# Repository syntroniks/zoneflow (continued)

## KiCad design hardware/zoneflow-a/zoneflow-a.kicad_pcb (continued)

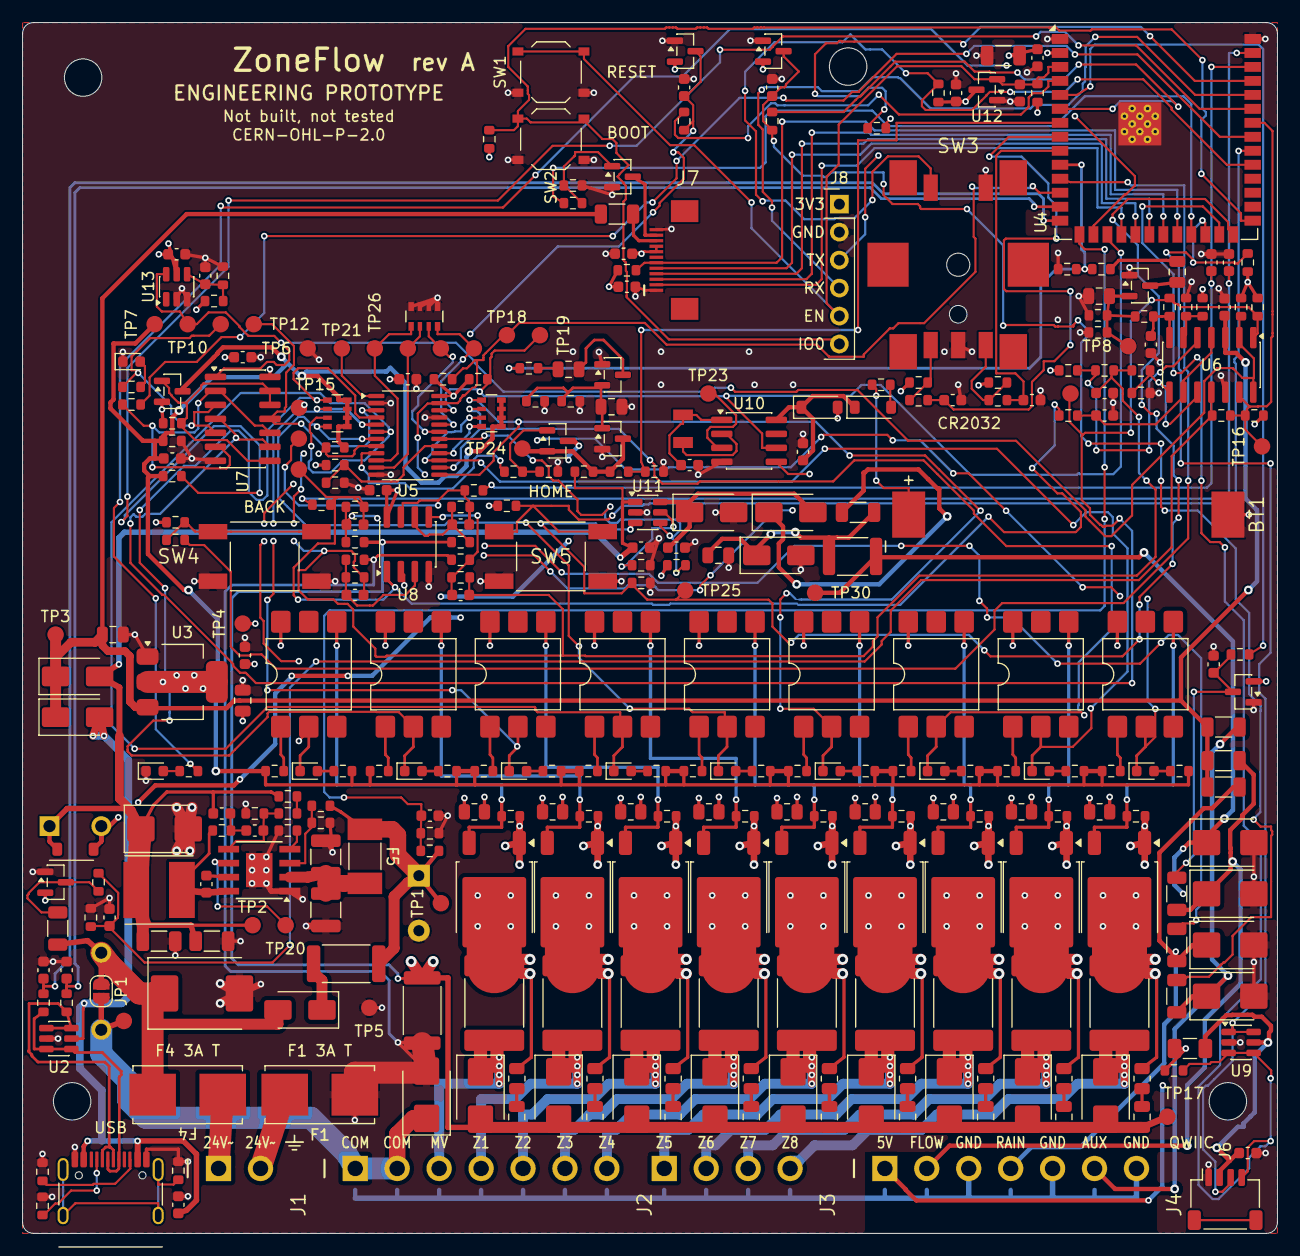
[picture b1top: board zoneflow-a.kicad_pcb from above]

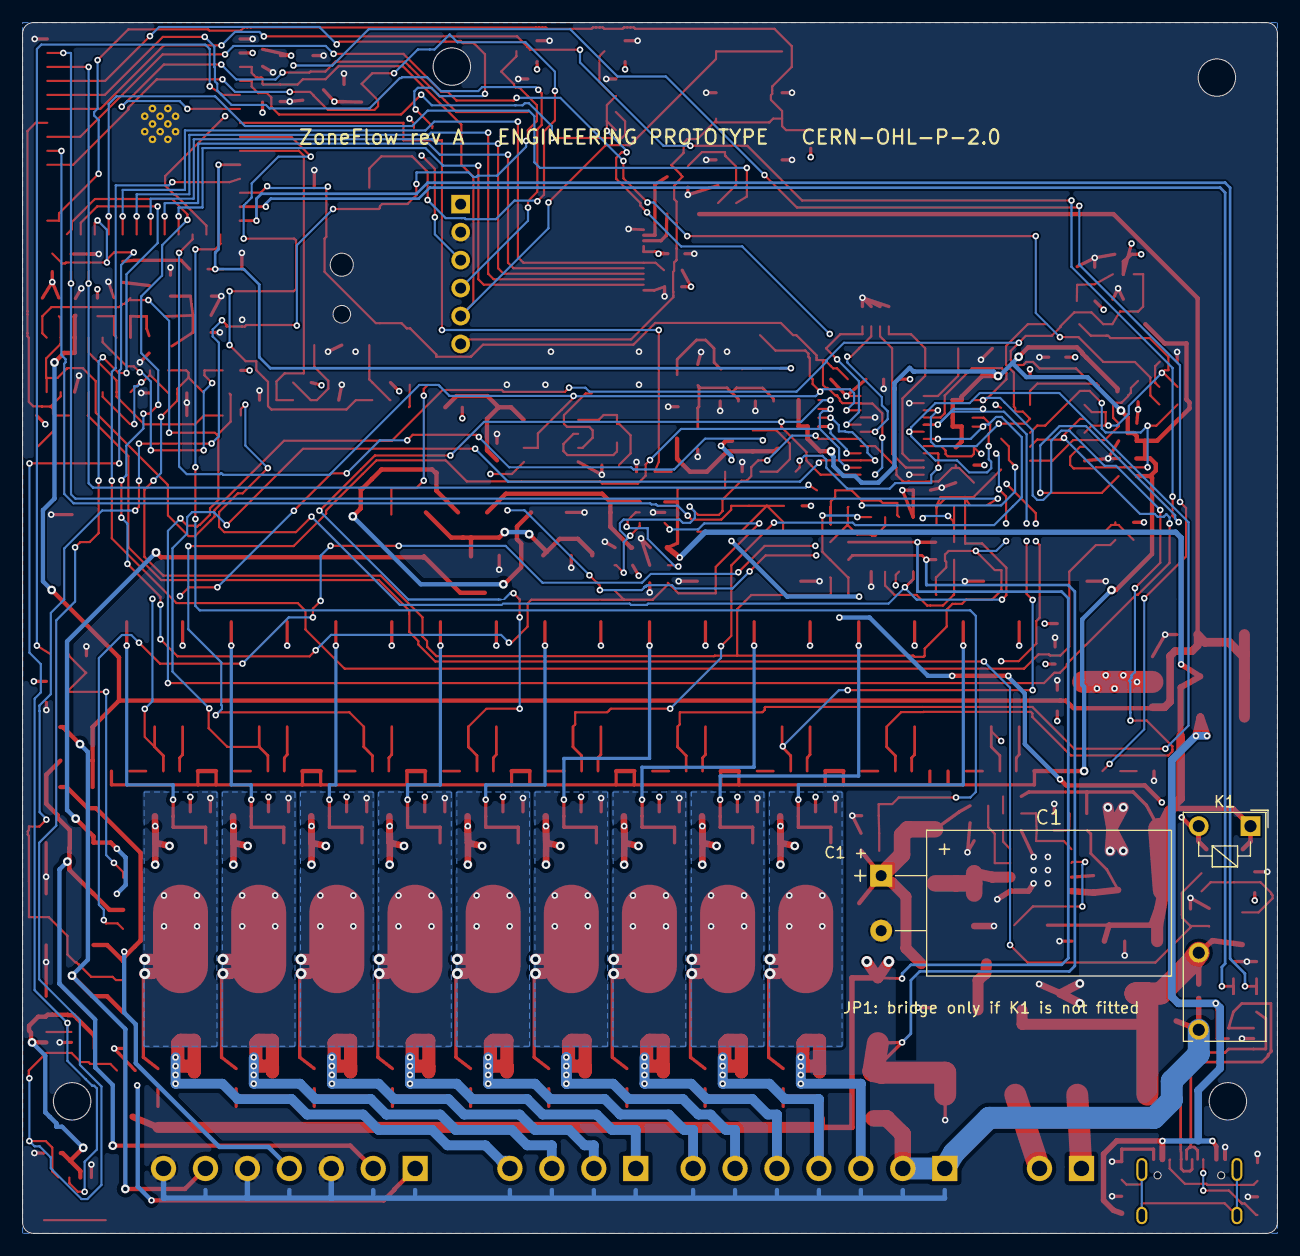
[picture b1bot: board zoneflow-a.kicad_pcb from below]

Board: 4 copper layers, 114.0 x 110.0 mm, 351 parts (2 on the bottom side), 198 nets.

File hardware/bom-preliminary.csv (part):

refs,qty_8zone,qty_4zone,value,package,manufacturer,mpn,lcsc,jlcpcb_library,jlcpcb_stock,usd_each_at_10,usd_each_at_100,usd_each_at_1000,source_url,datasheet_url,datasheet,date_checked,note
J1,1,1,"Header 2-way 3.81 mm pluggable, right angle",THT,Cixi Kefa Elec,KF2EDGR-3.81-2P,C441182,extended,45747,0.0537,0.0436,0.03,https://www.lcsc.com/product-detail/pluggable-system-termina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,https://www.lcsc.com/datasheet/lcsc_datasheet_2303311930_Cix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,listing only,2026-11-10,Mates with plug KF2EDGK-3.81-2P
F1 F4,2,2,Fuse 3 A time-lag in SMD holder,SMD 9.7x5 mm,Littelfuse,0154003.DRT,C206913,extended,2514,1.5283,1.1879,1.111,https://www.lcsc.com/product-detail/disposable-fuses_littelf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,https://www.lcsc.com/datasheet/lcsc_datasheet_2401301225_Lit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,read,2026-11-10,Replacement fuse 0452003.MRL (C99550)
D1,1,1,TVS 48 V bidirectional 1500 W,SMC,Littelfuse,SMCJ48CA,C151287,extended,4645,0.2481,0.1974,0.1485,https://www.lcsc.com/product-detail/esd-and-surge-protection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,https://www.lcsc.com/datasheet/lcsc_datasheet_2304140030_Lit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,read,2026-11-10,
D2,1,1,Rectifier 1 A 1000 V,SMA,MDD(Microdiode Semiconductor),M7,C95872,basic,5405522,0.0103,0.0103,0.0085,https://www.lcsc.com/product-detail/diodes-general-purpose_m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,https://www.lcsc.com/datasheet/lcsc_datasheet_2407101107_MDD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,read,2026-11-10,
R1,1,1,"3R 5% 1 W, surge series",2512,YAGEO,SR2512JK-073RL,C2936639,extended,3972,0.1926,0.1504,0.1097,https://www.lcsc.com/product-detail/chip-resistor-surface-mo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,https://www.lcsc.com/datasheet/C2936639.pdf,read,2026-11-10,"Yageo SR series data sheet V.14, figure 7-2: about 750 W for 1 ms and 200 W for 10 ms single pulse in 2512 at 5 % tolerance. The 1 % SR2512FK parts follow figure 7-1 and take about 200 W at 1 ms, which is not enough"
C1,1,1,470 uF 63 V aluminium electrolytic,THT 12.5x20 mm,Rubycon,63ZLJ470M12.5X20,C2940725,extended,3180,0.3453,0.2537,0.2177,https://www.lcsc.com/product-detail/aluminum-electrolytic-ca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,https://www.lcsc.com/datasheet/C2940725.pdf,read,2026-11-10,"Through-hole, soldered by hand from the bottom side, lying down; not machine-fitted. Rubycon ZLJ sheet: 10000 h at 105 C, 2400 mA at 100 kHz, 1320 mA at 120 Hz. Same holes: Rubycon 63PX470MEFC12.5X20 (C88758, 2000 h, read) and AISHI ERS1JM471K20OT (C106675, listing only)"
F5,1,1,"Fuse 0.5 A very fast-acting, 125 V",2410,Littelfuse,0451.500MRL,C142836,extended,11512,0.2339,0.1908,0.1321,https://www.lcsc.com/product-detail/disposable-fuses_littelf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,https://www.lcsc.com/datasheet/lcsc_datasheet_1810280911_Lit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,read,2026-11-10,"Littelfuse 451/453 series: 0.42 ohm cold, nominal melting I2t 0.0824 A2s, interrupting 50 A at 125 V and 300 A at 32 V DC. Soldered: it opens only when U1 has failed. Do not fit a larger rating: the 0.42 ohm also limits the fault current to the interrupting rating"
C2 C3,2,2,2.2 uF 100 V X7R,1210,Samsung Electro-Mechanics,CL32B225KCJSNNE,C55151,extended,22064,0.2062,0.1658,0.1575,https://www.lcsc.com/product-detail/multilayer-ceramic-capac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,https://www.lcsc.com/datasheet/lcsc_datasheet_2304140030_Sam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,listing only,2026-11-10,
U1,1,1,LM5164DDAR 100 V 1 A synchronous buck,SO-8 PowerPAD,Texas Instruments,LM5164DDAR,C477928,extended,1840,2.1697,1.6739,1.5119,https://www.lcsc.com/product-detail/dc-dc-converters_texas-i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,https://www.ti.com/lit/ds/symlink/lm5164.pdf,read,2026-11-10,
C4,1,1,2.2 nF 50 V X7R,0603,FH (Guangdong Fenghua Advanced Tech),0603B222K500NT,C1604,basic,543476,0.0109,0.0109,0.0086,https://www.lcsc.com/product-detail/multilayer-ceramic-capac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,https://www.lcsc.com/datasheet/lcsc_datasheet_2304140030_FH-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,read,2026-11-11,"Fenghua general MLCC specification (the LCSC sheet for this number): X7R, +/-10 % (K), 50 V, -55 to 125 C, insulation resistance 10 Gohm minimum up to 25 nF. Replaces Samsung CL10B222KB8NNNC (C16033, extended) since the BOM consolidation; same value, dielectric, tolerance, voltage and package"
L1,1,1,"47 uH, Isat 2.0 A, 0.2R",6x6x4.5 mm,BOURNS,SRN6045TA-470M,C5151734,extended,4123,0.3608,0.2859,0.2047,https://www.lcsc.com/product-detail/power-inductors_bourns-s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,https://wmsc.lcsc.com/wmsc/upload/file/pdf/v2/lcsc/220825180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,read,2026-11-10,
C5 C6 C14,3,3,22 uF 25 V X5R,1206,Samsung Electro-Mechanics,CL31A226KAHNNNE,C12891,basic,1976907,0.1028,0.1028,0.0724,https://www.lcsc.com/product-detail/multilayer-ceramic-capac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,https://www.lcsc.com/datasheet/lcsc_datasheet_2304140030_Sam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,listing only,2026-11-10,
R2,1,1,47k 1%,0603,UNI-ROYAL(Uniroyal Elec),0603WAF4702T5E,C25819,basic,3006958,0.0016,0.0016,0.0012,https://www.lcsc.com/product-detail/chip-resistor-surface-mo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,https://www.lcsc.com/datasheet/lcsc_datasheet_2206010045_UNI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,listing only,2026-11-10,
R3,1,1,330k 1%,0603,UNI-ROYAL(Uniroyal Elec),0603WAF3303T5E,C23137,basic,678476,0.0016,0.0016,0.0012,https://www.lcsc.com/product-detail/chip-resistor-surface-mo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,https://www.lcsc.com/datasheet/lcsc_datasheet_2206010116_UNI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,listing only,2026-11-10,
R4 R10 R18 R19 R26 R27 R35 R36 R39 R41 R52 R53 R56 R58 R63 R69 R70 R72 R85 R87 R88 R93,22,22,10k 1%,0603,UNI-ROYAL(Uniroyal Elec),0603WAF1002T5E,C25804,basic,45615451,0.0022,0.0022,0.0018,https://www.lcsc.com/product-detail/chip-resistor-surface-mo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,https://www.lcsc.com/datasheet/lcsc_datasheet_2206010045_UNI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,listing only,2026-11-10,
R5 R12 R14 R25 R31 R62 R86 R90 R94 R96,10,10,100k 1%,0603,UNI-ROYAL(Uniroyal Elec),0603WAF1003T5E,C25803,basic,15636901,0.0029,0.0029,0.0023,https://www.lcsc.com/product-detail/chip-resistor-surface-mo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,https://www.lcsc.com/datasheet/lcsc_datasheet_2206010045_UNI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,listing only,2026-11-10,
R30 R91 R100,3,3,110k 1%,0603,UNI-ROYAL(Uniroyal Elec),0603WAF1103T5E,C25805,extended (preferred),180061,0.0028,0.0028,0.0021,https://www.lcsc.com/product-detail/chip-resistor-surface-mo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,https://www.lcsc.com/datasheet/C25805.pdf,listing only,2026-11-10,
R95,1,1,150k 1%,0603,UNI-ROYAL(Uniroyal Elec),0603WAF1503T5E,C22807,basic,701846,0.0017,0.0017,0.0013,https://www.lcsc.com/product-detail/chip-resistor-surface-mo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,https://www.lcsc.com/datasheet/C22807.pdf,listing only,2026-11-10,
RN1 RN2 RN3,3,3,100k x4 5% resistor array,0603x4,UNI-ROYAL(Uniroyal Elec),4D03WGJ0104T5E,C1996,extended,7320,0.0103,0.0103,0.0083,https://www.lcsc.com/product-detail/resistor-networks-arrays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,https://www.lcsc.com/datasheet/C1996.pdf,read,2026-11-10,"Four isolated resistors, convex 4D03. Pin pairs 1-8, 2-7, 3-6, 4-5 assumed from the usual numbering; the data sheet shows the circuit as a picture. Confirm at capture"
R6 R8 R83,3,3,200k 1%,0603,UNI-ROYAL(Uniroyal Elec),0603WAF2003T5E,C25811,basic,1820047,0.0021,0.0021,0.0016,https://www.lcsc.com/product-detail/chip-resistor-surface-mo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,https://www.lcsc.com/datasheet/lcsc_datasheet_2206010045_UNI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,listing only,2026-11-10,
C7,1,1,3.3 nF 50 V X7R,0603,Samsung Electro-Mechanics,CL10B332KB8NNNC,C1613,basic,364454,0.0088,0.0088,0.0063,https://www.lcsc.com/product-detail/multilayer-ceramic-capac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,https://www.lcsc.com/datasheet/lcsc_datasheet_2304140030_Sam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,listing only,2026-11-10,
C8,1,1,100 pF 50 V C0G,0603,Samsung Electro-Mechanics,CL10C101JB8NNNC,C14858,basic,3768735,0.0082,0.0082,0.0062,https://www.lcsc.com/product-detail/multilayer-ceramic-capac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,https://www.lcsc.com/datasheet/lcsc_datasheet_2304140030_Sam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,listing only,2026-11-10,
R7 R13 R57,3,3,1M 1%,0603,UNI-ROYAL(Uniroyal Elec),0603WAF1004T5E,C22935,basic,4167811,0.0018,0.0018,0.0014,https://www.lcsc.com/product-detail/chip-resistor-surface-mo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,https://www.lcsc.com/datasheet/lcsc_datasheet_2206010130_UNI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,listing only,2026-11-10,
R9,1,1,300k 1%,0603,UNI-ROYAL(Uniroyal Elec),0603WAF3003T5E,C23024,basic,454953,0.0038,0.0038,0.0029,https://www.lcsc.com/product-detail/chip-resistor-surface-mo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,https://www.lcsc.com/datasheet/lcsc_datasheet_2206010116_UNI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,listing only,2026-11-10,
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
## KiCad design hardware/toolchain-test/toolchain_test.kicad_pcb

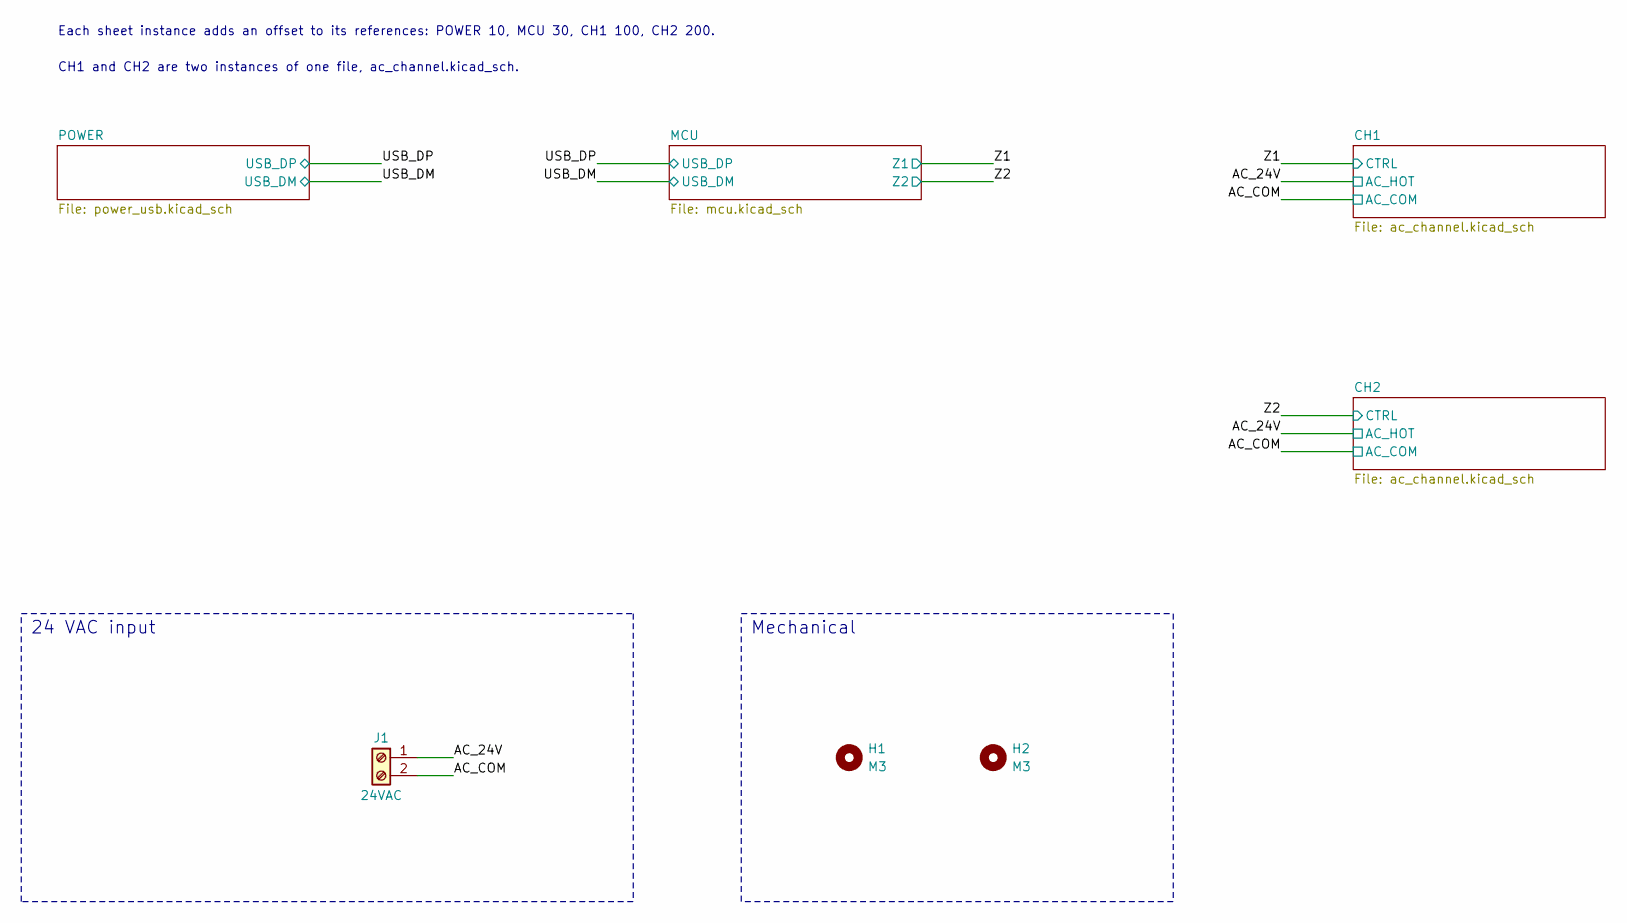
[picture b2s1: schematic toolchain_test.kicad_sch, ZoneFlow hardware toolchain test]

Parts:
H1, H2: M3; MountingHole_3.2mm_M3
J1: 24VAC; TerminalBlock_Phoenix_MKDS-1,5-2-5.08_1x02_P5.08mm_Horizont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; LCSC C474952

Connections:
/AC_24V: J1.1; also elsewhere on the board
/AC_COM: J1.2; also elsewhere on the board

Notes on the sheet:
24 VAC input
Each sheet instance adds an offset to its references: POWER 10, MCU 30, CH1 100, CH2 200.
Mechanical
CH1 and CH2 are two instances of one file, ac_channel.kicad_sch.

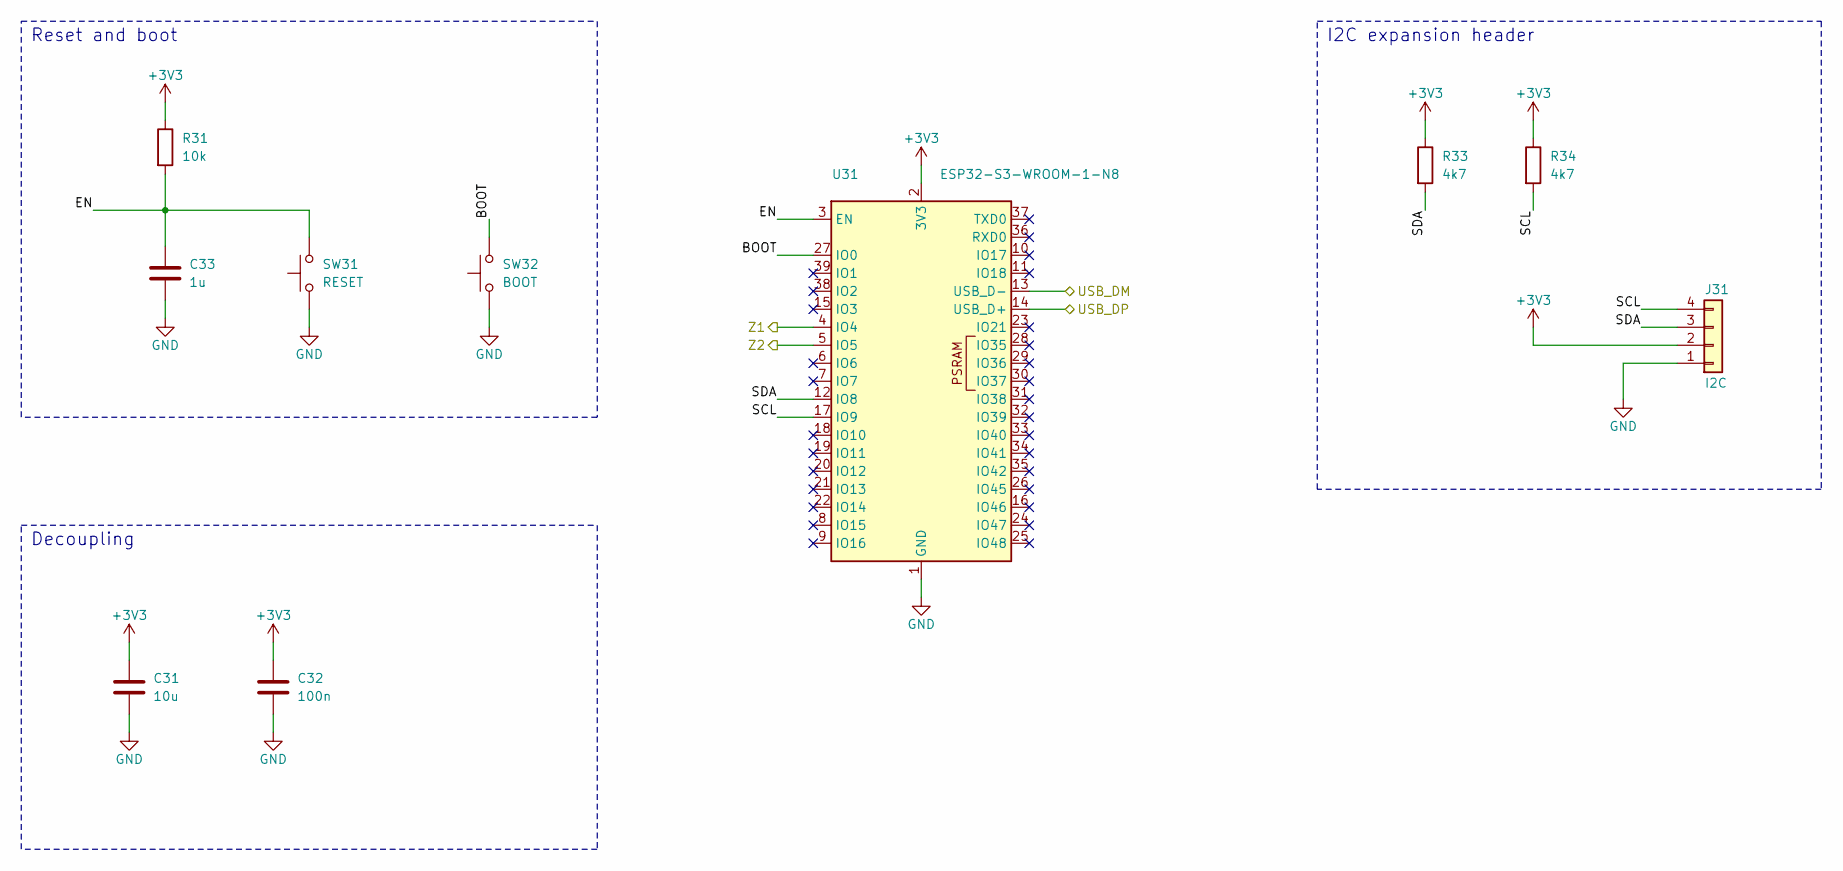
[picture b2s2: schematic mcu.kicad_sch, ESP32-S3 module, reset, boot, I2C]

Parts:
C31: 10u; C_0805_2012Metric; LCSC C15850
C32: 100n; C_0603_1608Metric; LCSC C14663
C33: 1u; C_0603_1608Metric; LCSC C15849
J31: I2C; PinHeader_1x04_P2.54mm_Vertical; LCSC C2905435
R31: 10k; R_0603_1608Metric; LCSC C25804
R33, R34: 4k7; R_0603_1608Metric; LCSC C23162
SW31: RESET; SW_SPST_TL3342; LCSC C2886898
SW32: BOOT; SW_SPST_TL3342; LCSC C2886898
U31: ESP32-S3-WROOM-1-N8; ESP32-S3-WROOM-1; LCSC C2913198

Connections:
+3V3: C31.1, C32.1, J31.2, R31.1, R33.1, R34.1, U31.2 (3V3); also elsewhere on the board
/MCU/BOOT: SW32.2, U31.27 (IO0)
/MCU/EN: C33.1, R31.2, SW31.2, U31.3 (EN)
/MCU/SCL: J31.4, R34.2, U31.17 (IO9)
/MCU/SDA: J31.3, R33.2, U31.12 (IO8)
/USB_DM: U31.13 (USB_D-); also elsewhere on the board
/USB_DP: U31.14 (USB_D+); also elsewhere on the board
/Z1: U31.4 (IO4); also elsewhere on the board
/Z2: U31.5 (IO5); also elsewhere on the board
GND: C31.2, C32.2, C33.2, J31.1, SW31.1, SW32.1, U31.1 (GND), U31.40 (GND), U31.41 (GND); also elsewhere on the board

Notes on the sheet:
Reset and boot
I2C expansion header
Decoupling

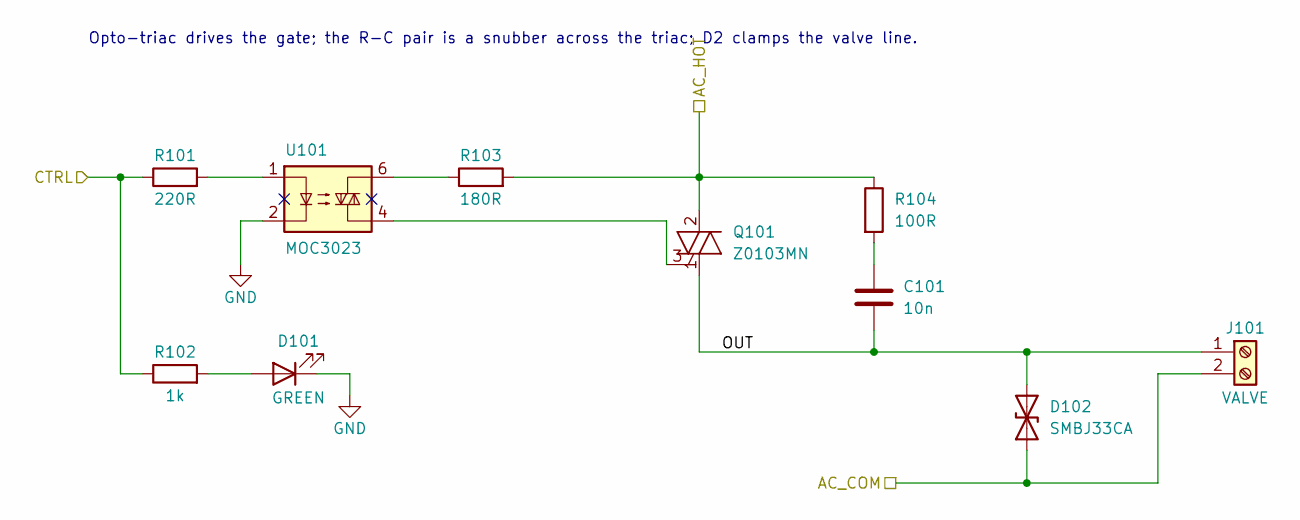
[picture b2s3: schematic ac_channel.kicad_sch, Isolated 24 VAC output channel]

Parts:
C101: 10n; C_0805_2012Metric; LCSC C1710
D101: GREEN; LED_0603_1608Metric; LCSC C72043
D102: SMBJ33CA; D_SMB; LCSC C78420
J101: VALVE; TerminalBlock_Phoenix_MKDS-1,5-2-5.08_1x02_P5.08mm_Horizont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; LCSC C474952
Q101: Z0103MN; SOT-223; LCSC C163595
R101: 220R; R_0603_1608Metric; LCSC C22962
R102: 1k; R_0603_1608Metric; LCSC C21190
R103: 180R; R_0603_1608Metric; LCSC C22828
R104: 100R; R_1206_3216Metric; LCSC C17901
U101: MOC3023; SMDIP-6_W9.53mm; LCSC C115469

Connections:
/AC_24V: Q101.2 (A2), Q101.4 (A4), R103.2, R104.1; also elsewhere on the board
/AC_COM: D102.1 (A1), J101.2; also elsewhere on the board
/CH1/OUT: C101.2, D102.2 (A2), J101.1, Q101.1 (A1)
/Z1: R101.1, R102.1; also elsewhere on the board
GND: D101.1 (K), U101.2; also elsewhere on the board
unnamed: C101.1, R104.2
unnamed: D101.2 (A), R102.2
unnamed: Q101.3 (G), U101.4
unnamed: R101.2, U101.1
unnamed: R103.1, U101.6

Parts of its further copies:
C201: 10n; C_0805_2012Metric; LCSC C1710
D201: GREEN; LED_0603_1608Metric; LCSC C72043
D202: SMBJ33CA; D_SMB; LCSC C78420
J201: VALVE; TerminalBlock_Phoenix_MKDS-1,5-2-5.08_1x02_P5.08mm_Horizont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; LCSC C474952
Q201: Z0103MN; SOT-223; LCSC C163595
R201: 220R; R_0603_1608Metric; LCSC C22962
R202: 1k; R_0603_1608Metric; LCSC C21190
R203: 180R; R_0603_1608Metric; LCSC C22828
R204: 100R; R_1206_3216Metric; LCSC C17901
U201: MOC3023; SMDIP-6_W9.53mm; LCSC C115469

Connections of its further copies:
/AC_24V: Q201.2 (A2), Q201.4 (A4), R203.2, R204.1; also elsewhere on the board
/AC_COM: D202.1 (A1), J201.2; also elsewhere on the board
/CH2/OUT: C201.2, D202.2 (A2), J201.1, Q201.1 (A1)
/Z2: R201.1, R202.1; also elsewhere on the board
GND: D201.1 (K), U201.2; also elsewhere on the board
unnamed: C201.1, R204.2
unnamed: D201.2 (A), R202.2
unnamed: Q201.3 (G), U201.4
unnamed: R201.2, U201.1
unnamed: R203.1, U201.6

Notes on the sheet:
Opto-triac drives the gate; the R-C pair is a snubber across the triac; D2 clamps the valve line.

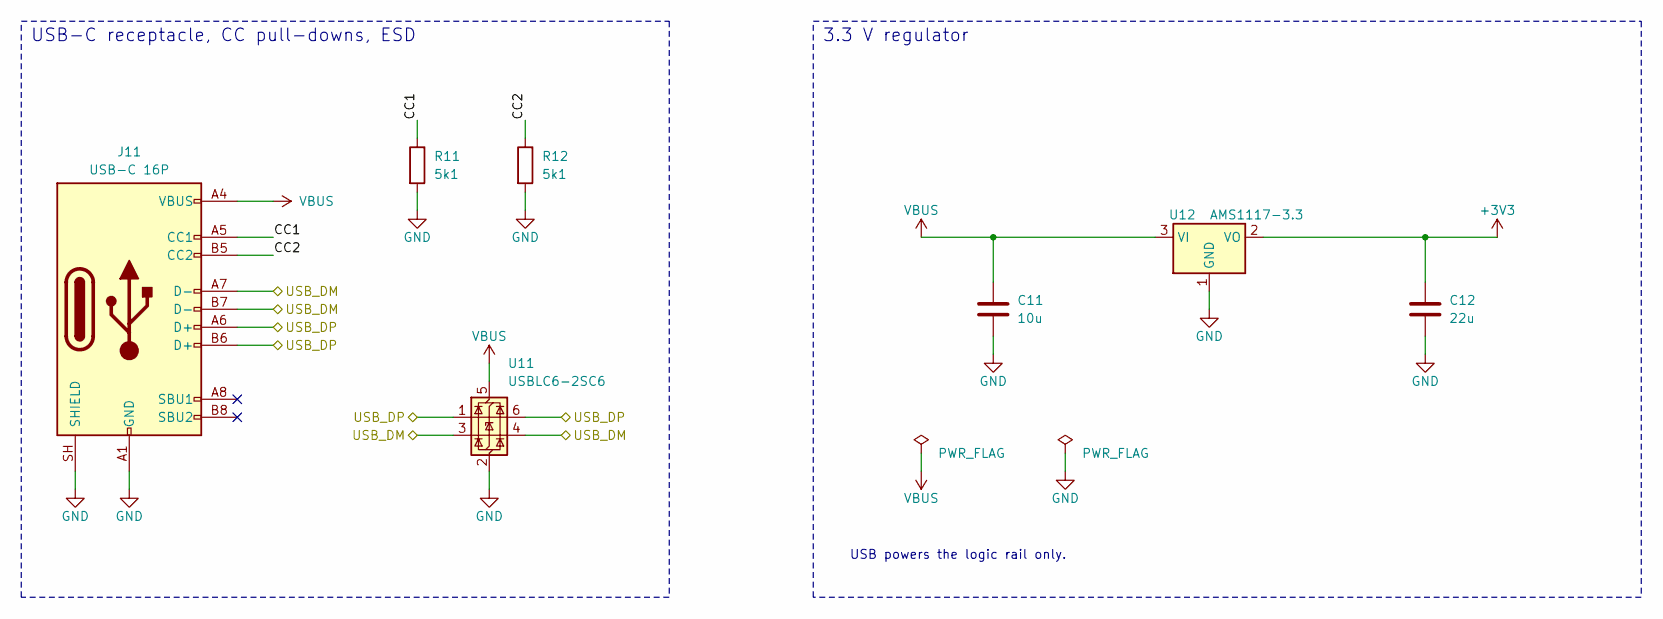
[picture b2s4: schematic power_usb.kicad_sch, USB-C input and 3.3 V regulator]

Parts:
C11: 10u; C_0805_2012Metric; LCSC C15850
C12: 22u; C_0805_2012Metric; LCSC C45783
J11: USB-C 16P; USB_C_Receptacle_HRO_TYPE-C-31-M-12; LCSC C165948
R11, R12: 5k1; R_0603_1608Metric; LCSC C23186
U11: USBLC6-2SC6; SOT-23-6; LCSC C7519
U12: AMS1117-3.3; SOT-223-3_TabPin2; LCSC C6186

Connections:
+3V3: C12.1, U12.2 (VO); also elsewhere on the board
/POWER/CC1: J11.A5 (CC1), R11.1
/POWER/CC2: J11.B5 (CC2), R12.1
/USB_DM: J11.A7 (D-), J11.B7 (D-), U11.3 (I/O2), U11.4 (I/O2); also elsewhere on the board
/USB_DP: J11.A6 (D+), J11.B6 (D+), U11.1 (I/O1), U11.6 (I/O1); also elsewhere on the board
GND: C11.2, C12.2, J11.A1 (GND), J11.A12 (GND), J11.B1 (GND), J11.B12 (GND), J11.SH (SHIELD), R11.2, R12.2, U11.2 (GND), U12.1 (GND); also elsewhere on the board
VBUS: C11.1, J11.A4 (VBUS), J11.A9 (VBUS), J11.B4 (VBUS), J11.B9 (VBUS), U11.5 (VBUS), U12.3 (VI)

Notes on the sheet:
USB-C receptacle, CC pull-downs, ESD
3.3 V regulator
USB powers the logic rail only.

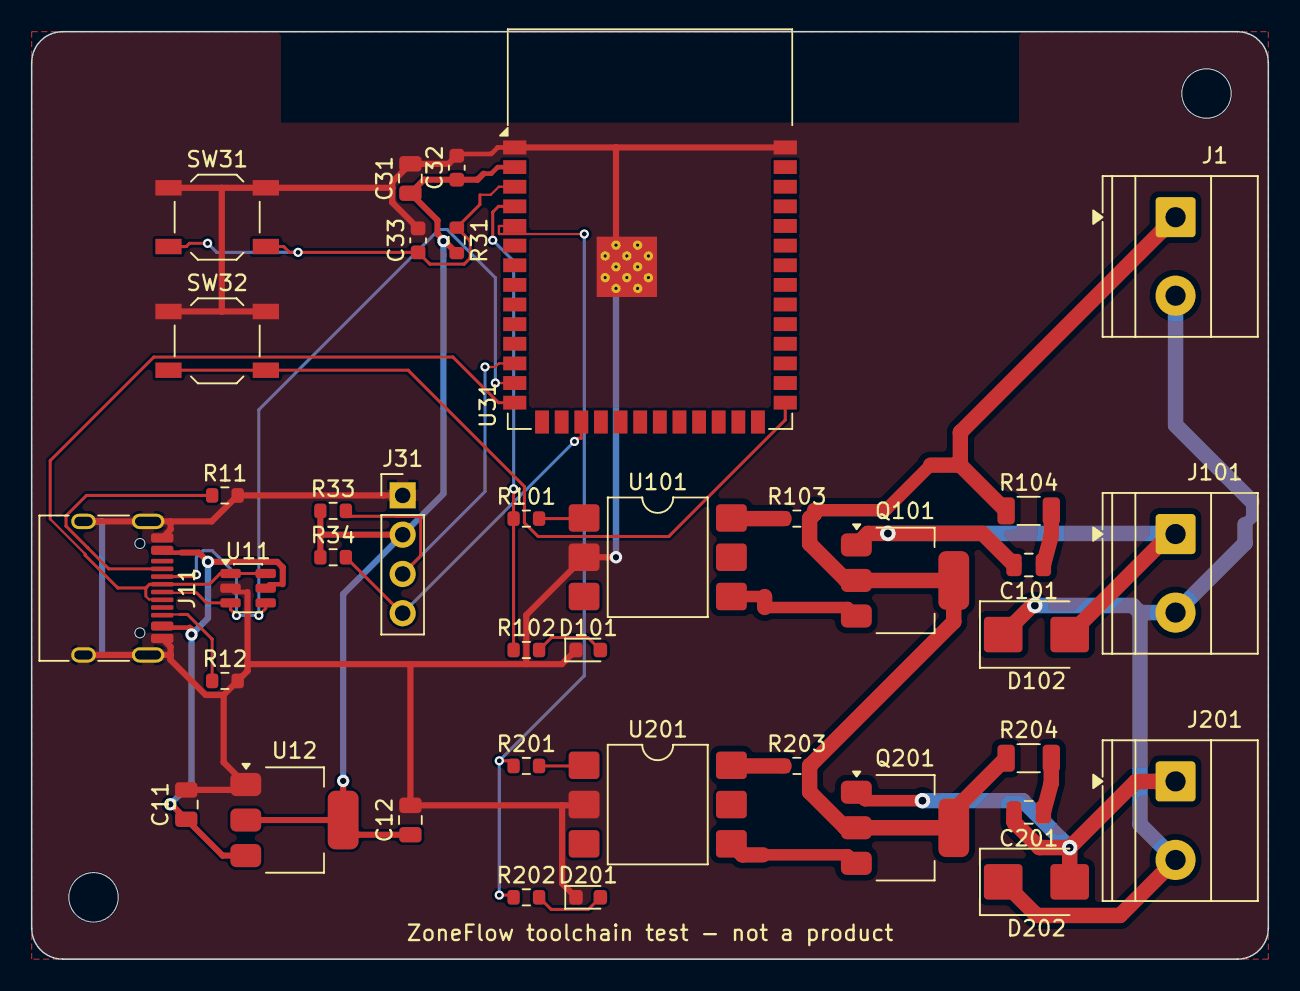
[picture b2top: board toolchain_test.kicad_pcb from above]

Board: 2 copper layers, 80.0 x 60.0 mm, 40 parts (0 on the bottom side), 27 nets.

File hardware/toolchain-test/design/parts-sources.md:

# Part number sources for the toolchain test

The test circuit is not a design; these parts were chosen only to fill the
`LCSC` field with real numbers. Each number was looked up on 2026-11-10 with a
web search and matched to the manufacturer part number on the listing named
in the last column. Stock and price were not checked. Electrical suitability
was not checked. Do not reuse this list for the ZoneFlow board without
reading the datasheets.

| LCSC | Manufacturer part | Used as | Listing read |
|---|---|---|---|
| C165948 | Korean Hroparts Elec TYPE-C-31-M-12 | J11 USB-C receptacle, 16 pin | https://lcsc.com/product-detail/C165948.html |
| C2913198 | Espressif ESP32-S3-WROOM-1-N8 | U31 | https://www.lcsc.com/product-detail/C2913198.html |
| C7519 | STMicroelectronics USBLC6-2SC6 | U11 USB ESD | https://www.lcsc.com/product-detail/C7519.html |
| C6186 | Advanced Monolithic Systems AMS1117-3.3, SOT-223 | U12 | https://www.lcsc.com/product-detail/C6186.html |
| C115469 | Lite-On MOC3023S-TA1, SMD-6 | U101, U201 opto-triac | https://www.lcsc.com/product-detail/C115469.html |
| C163595 | STMicroelectronics Z0103MN5AA4, SOT-223 | Q101, Q201 triac | https://www.lcsc.com/product-detail/C163595.html |
| C78420 | Brightking SMBJ33CA, SMB | D102, D202 clamp | https://www.lcsc.com/product-detail/C78420.html |
| C72043 | Everlight 19-217/GHC-YR1S2/3T, 0603 green | D101, D201 | https://lcsc.com/product-detail/C72043.html |
| C474952 | Cixi Kefa KF128-5.08-2P-AA, 2 pin 5.08 mm | J1, J101, J201 screw terminal | https://www.lcsc.com/product-detail/C474952.html |
| C2905435 | kinghelm KH-2.54PH180-1X4P-L11.5 | J31 1x4 header | https://www.lcsc.com/product-detail/C2905435.html |
| C2886898 | E-Switch TL3342F160QG | SW31, SW32 | https://www.lcsc.com/product-detail/C2886898.html |
| C23186 | UNI-ROYAL 0603WAF5101T5E, 5.1 k 0603 | R11, R12 | https://jlcpcb.com/partdetail/0603WAF5101T5E/C23186 |
| C25804 | UNI-ROYAL 0603WAF1002T5E, 10 k 0603 | R31 | https://jlcpcb.com/partdetail/0603WAF1002T5E/C25804 |
| C23162 | UNI-ROYAL 0603WAF4701T5E, 4.7 k 0603 | R33, R34 | https://jlcpcb.com/partdetail/0603WAF4701T5E/C23162 |
| C22962 | UNI-ROYAL 0603WAF2200T5E, 220 R 0603 | R101, R201 | https://jlcpcb.com/partdetail/0603WAF2200T5E/C22962 |
| C21190 | UNI-ROYAL 0603WAF1001T5E, 1 k 0603 | R102, R202 | https://jlcpcb.com/partdetail/0603WAF1001T5E/C21190 |
| C22828 | UNI-ROYAL 0603WAF1800T5E, 180 R 0603 | R103, R203 | https://jlcpcb.com/partdetail/23555-0603WAF1800T5E/C22828 |
| C17901 | UNI-ROYAL 1206W4F1000T5E, 100 R 1206 | R104, R204 | https://jlcpcb.com/partdetail/1206W4F1000T5E/C17901 |
| C15850 | Samsung CL21A106KAYNNNE, 10 uF 25 V 0805 | C11, C31 | https://www.lcsc.com/product-detail/C15850.html |
| C45783 | Samsung CL21A226MAQNNNE, 22 uF 25 V 0805 | C12 | https://www.lcsc.com/product-detail/C45783.html |
| C14663 | YAGEO CC0603KRX7R9BB104, 100 nF 50 V 0603 | C32 | https://www.lcsc.com/product-detail/_YAGEO-_C14663.html |
| C15849 | Samsung CL10A105KB8NNNC, 1 uF 50 V 0603 | C33 | https://www.lcsc.com/product-detail/C15849.html |
| C1710 | Samsung CL21B103KBANNNC, 10 nF 50 V 0805 | C101, C201 | https://jlcpcb.com/partdetail/CL21B103KBANNNC/C1710 |

Known mismatches between these parts and the KiCad footprints used, left
as they are because the footprints only have to exercise the flow:

- The terminal blocks use KiCad's Phoenix MKDS 1,5/2-5.08 footprint; the
  listed part is a KF128, not checked for the same pin layout.
- The opto-triac uses `SMDIP-6_W9.53mm`; the MOC3023S land pattern was not
  compared with it.

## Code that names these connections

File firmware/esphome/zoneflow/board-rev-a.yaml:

# GENERATED from hardware/pinmap.yaml by firmware/esphome/tools/gen_board_yaml.py.
# Do not edit. Change the pin map and run the script; CI fails when this file is stale.
# Board: zoneflow revision A, ESP32-S3-WROOM-1-N16R8.
substitutions:
  zf_pin_isense_lo: "GPIO1"  # ISENSE_LO
  zf_pin_isense_hi: "GPIO2"  # ISENSE_HI
  zf_pin_vin_monitor: "GPIO3"  # VIN_MON
  zf_pin_rain: "GPIO4"  # SENS_RAIN
  zf_pin_flow: "GPIO5"  # SENS_FLOW
  zf_pin_aux: "GPIO6"  # SENS_AUX
  zf_pin_relay_readback: "GPIO7"  # RLY_B_RB
  zf_pin_i2c_sda: "GPIO8"  # I2C0_SDA
  zf_pin_i2c_scl: "GPIO9"  # I2C0_SCL
  zf_pin_tft_cs: "GPIO10"  # TFT_CS
  zf_pin_tft_mosi: "GPIO11"  # TFT_MOSI
  zf_pin_tft_sclk: "GPIO12"  # TFT_SCLK
  zf_pin_tft_dc: "GPIO13"  # TFT_DC
  zf_pin_tft_reset: "GPIO14"  # TFT_RST
  zf_pin_encoder_a: "GPIO15"  # ENC_A
  zf_pin_encoder_b: "GPIO16"  # ENC_B
  zf_pin_encoder_switch: "GPIO38"  # ENC_SW
  zf_pin_button_back: "GPIO18"  # BTN_BACK
  zf_pin_backlight: "GPIO21"  # TFT_BL
  zf_pin_keepalive: "GPIO17"  # KEEPALIVE
  zf_pin_button_home: "GPIO39"  # BTN_HOME
  zf_pin_overcurrent: "GPIO40"  # OC_FAULT_N
  zf_pin_zero_cross: "GPIO41"  # AC_ZC
  zf_pin_drive_readback: "GPIO42"  # DRV_EN_RB
  zf_pin_sensor_supply: "GPIO45"  # SENS_PWR_EN
  zf_pin_status_led: "GPIO46"  # STATUS_LED
  zf_pin_qwiic_sda: "GPIO47"  # QWIIC_SDA
  zf_pin_qwiic_scl: "GPIO48"  # QWIIC_SCL
  zf_bit_zone1: "0.0"  # ZONE1, expander port.bit
  zf_bit_zone2: "0.1"  # ZONE2, expander port.bit
  zf_bit_zone3: "0.2"  # ZONE3, expander port.bit
  zf_bit_zone4: "0.3"  # ZONE4, expander port.bit
  zf_bit_zone5: "1.0"  # ZONE5, expander port.bit
  zf_bit_zone6: "1.1"  # ZONE6, expander port.bit
  zf_bit_zone7: "1.2"  # ZONE7, expander port.bit
  zf_bit_zone8: "1.3"  # ZONE8, expander port.bit
  zf_bit_master: "0.4"  # MASTER, expander port.bit
  zf_bit_relay: "0.5"  # COM_RELAY, expander port.bit
  zf_bit_variant_8zone_n: "1.4"  # VARIANT_8ZONE_N, expander port.bit
  zf_bit_sensor_fault_n: "1.5"  # SENS_PWR_FAULT_N, expander port.bit
  zf_i2c_frequency: "400000"
  zf_expander_address: "0x74"  # TCA9539PWR
  zf_rtc_address: "0x51"  # PCF8563T
  zf_max_outputs_on: "3"
  zf_adc_attenuation: "6dB"

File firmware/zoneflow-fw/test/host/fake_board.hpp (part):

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    ToggleStrong, // a 0 ohm bridge to a net that toggles by itself (backlight, boot log): it wins
    ToggleWeak,   // a 1 kohm bridge to such a net: the pin wins while driven; floating, the net toggles
    HighStrong,   // KA shorted to 3V3
    HighWeak,     // a node of detector A shorted to 3V3 (KA_N0): the pin wins while driven, floating it reads high
};

class FakeBoard final : public hw::IExpanderBus {
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    bool sensorFault = false;
    bool acPresent = true;
    bool vBuck = true; // false: U1 failed and F5 open, logic on USB (rule 15)
    // VIN_MON, GPIO3: the mean of a 100 ms window, mV (hardware design
    // 19.10: 960 at 24 VAC, 40 VA, typical load). Without 24 VAC the
    // rectified supply is gone: 0.
    int32_t vinMonMv = 960;
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    int32_t noiseMa = 0;
    bool expanderIgnoresReset = false; // DRV_EN stuck high: the expander answers with no keep-alive
    bool expanderNeverActive = false;  // DRV_EN stuck low or RESET held: the expander never answers
    bool q3Shorted = false;            // V_DRV on whatever DRV_EN_N does (Q3, or GPIO42 driven high)
    bool vDrvNeverOn = false;          // V_DRV, or its read-back on GPIO42, never high
    bool r12Open = false;              // Q1's gate keeps its charge when RLY_ON is released
    // B_RB, GPIO7: forced low (R93 open, read-back shorted to ground, ...).
    bool relayReadbackLow = false;
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    bool pinIsInput() const { return pinInput_; }
    // DRV_EN: the expander is out of reset.
    bool drvEn() const { return !expanderNeverActive && ((a.level(kaNetHigh_) && !latched) || expanderIgnoresReset); }
    // V_DRV, the opto LED supply behind Q3, which GPIO42 reads since review A2.
    bool vDrv() const { return q3Shorted || (a.level(kaNetHigh_) && !latched && !vDrvNeverOn); }
    bool driveEnabled() const { return vDrv(); }
    bool expanderActive() const { return drvEn(); }
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    // Digital read of GPIO7: low under 0.25 VDD, high over 0.75 VDD. A level
    // between them is taken as high, the case only the analogue read finds.
    bool relayReadbackHigh() const { return relayReadbackMv() > 825; }
    // Valves whose opto LED is driven: the pin low and V_DRV on.
    bool valveDriven(std::size_t i) const
    {
        if (i >= 4 && i < 8 && !eightZone) {
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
